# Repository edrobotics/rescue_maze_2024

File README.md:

# Rescue Maze 2024

Repository for ED Robotics' participation in the Robocup Junior Rescue Maze 2024 competition.

The contents of this repository were used in RoboCup Junior SM (Swedish Championships) 2024.

The code and CAD models are provided as-is, without any additional work done after the competition. The code (and hardware) did not work as expected, so keep that in mind.

## Performance

- RoboCupJunior Sweden 2024: Last place, 5 points :(

## Conclusions

Minimum Viable Product is a good idea that probably should have been prioritised more.

## Note:

This was our second year doing robotics. The code may contain trace amounts of spaghetti.

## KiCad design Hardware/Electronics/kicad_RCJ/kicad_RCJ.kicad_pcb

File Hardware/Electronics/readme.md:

# Electronics
In this folder, all electronics-related things are stored. This is mostly schematics and PCBs.

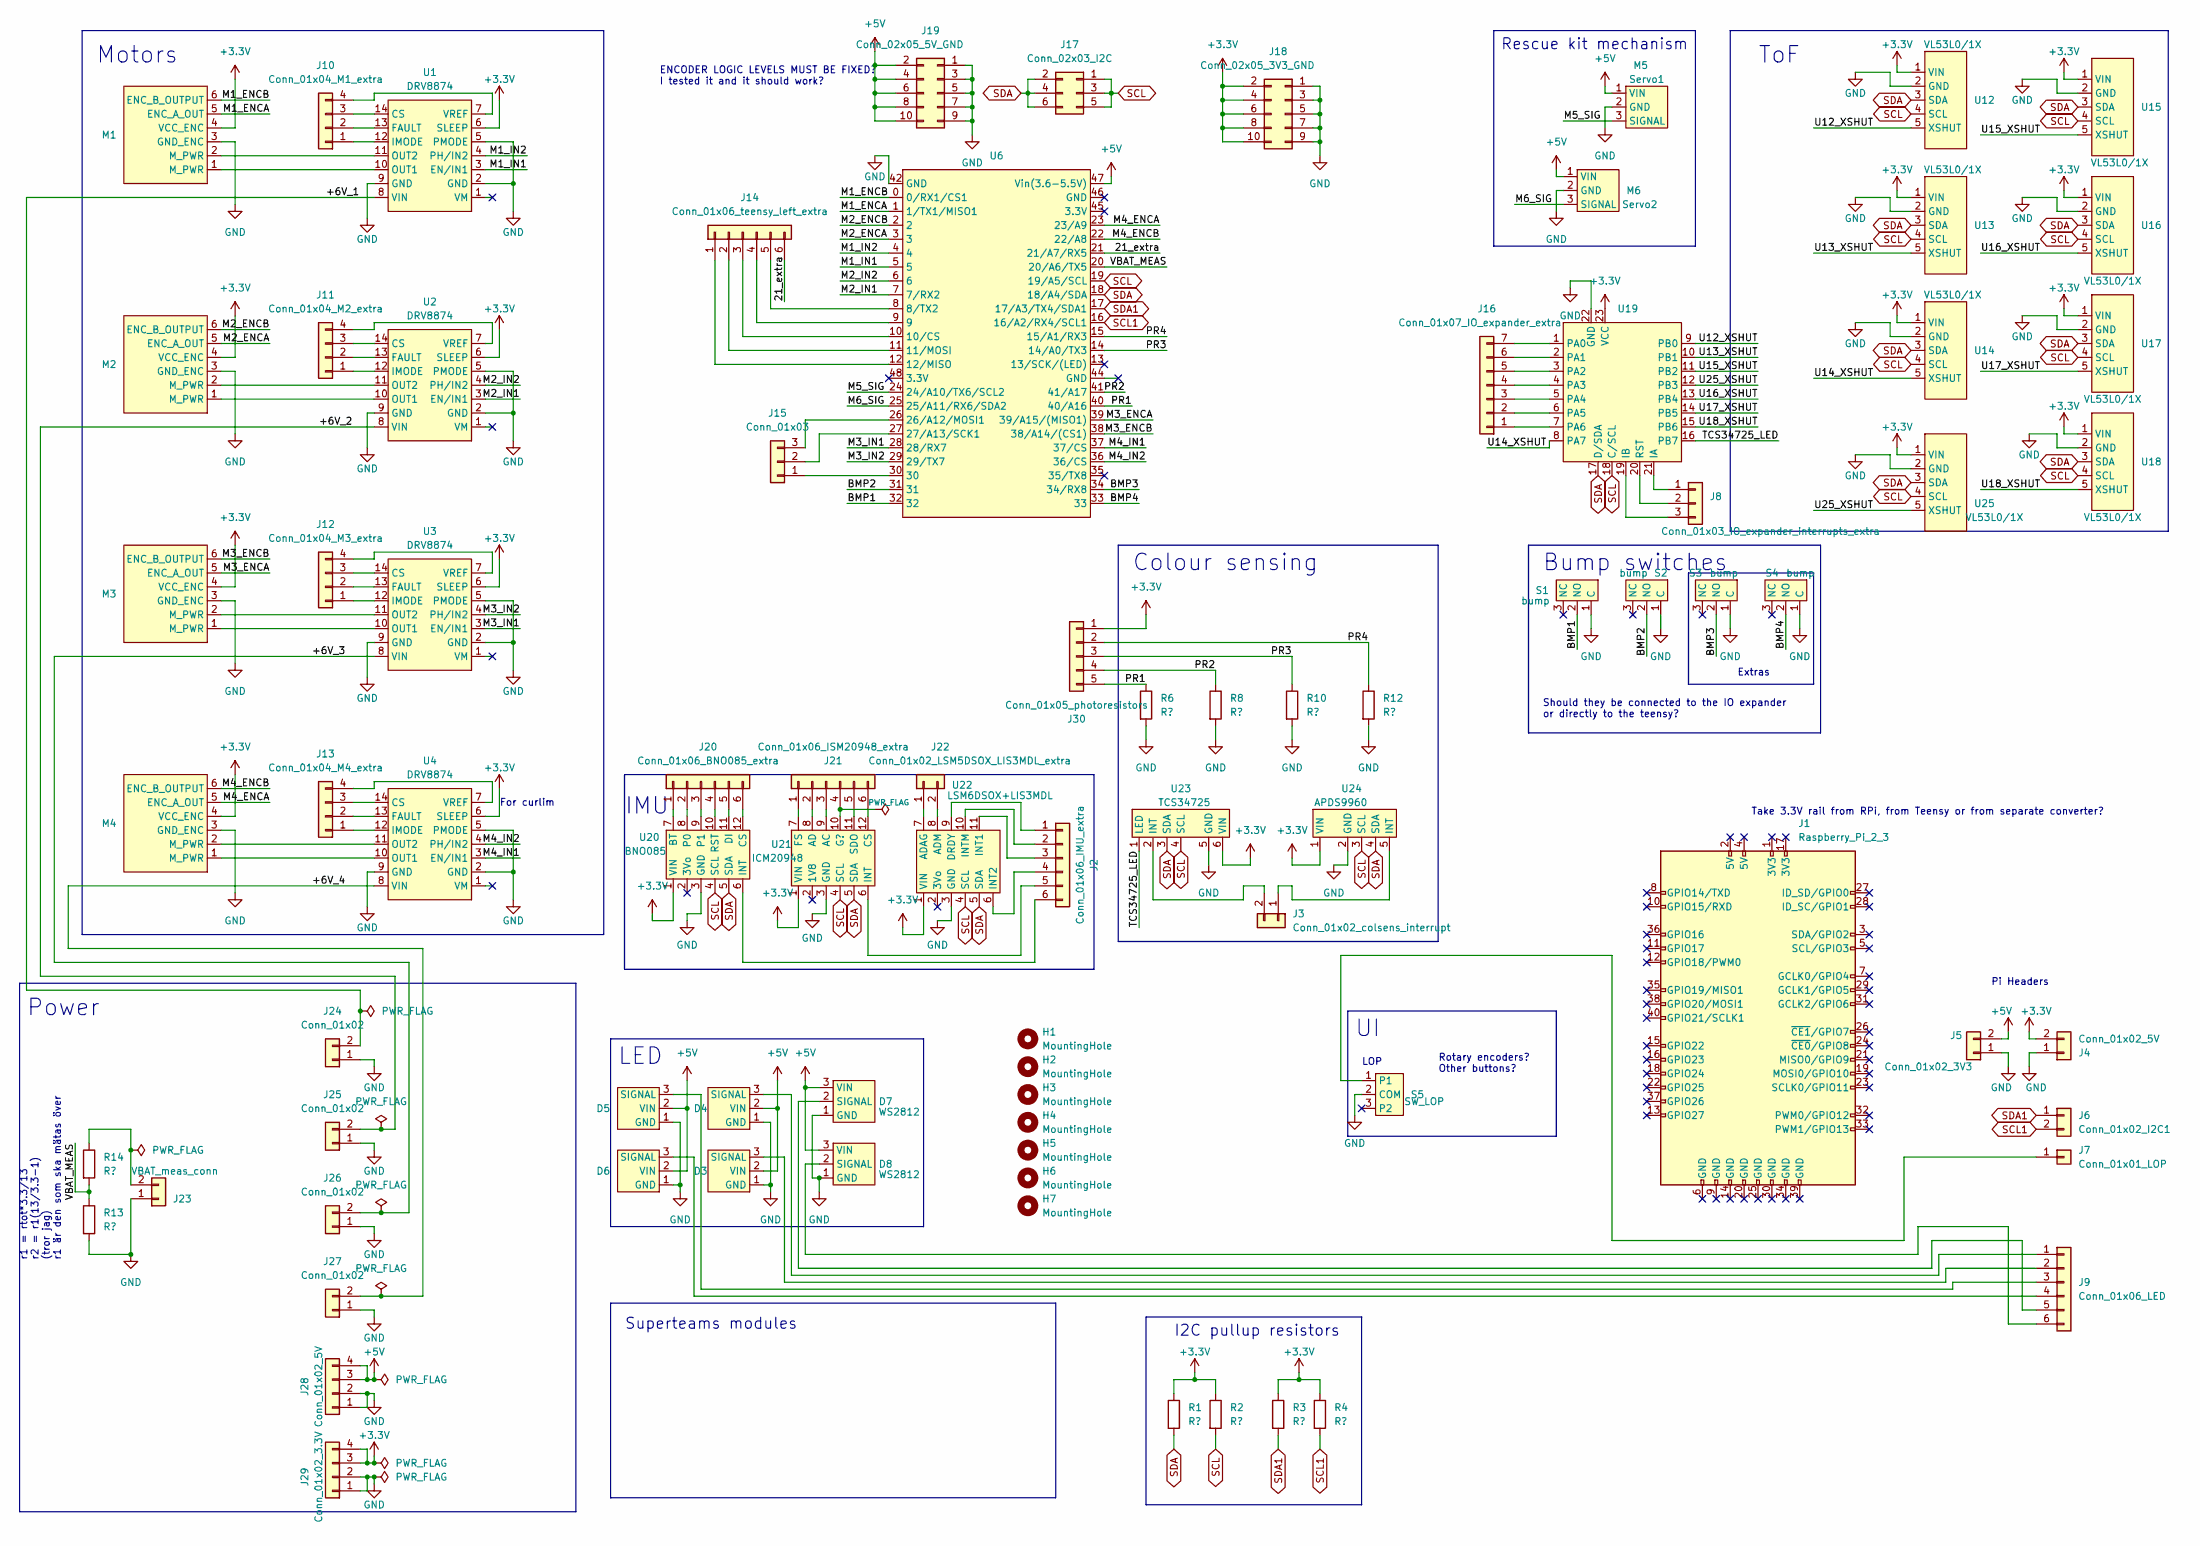
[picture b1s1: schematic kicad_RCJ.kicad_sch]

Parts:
D3, D4, D5, D6: PinSocket_1x03_P2.54mm_Vertical
D7, D8: WS2812; PinSocket_1x03_P2.54mm_Vertical
H1, H2, H3, H4, H5, H6, H7: MountingHole; MountingHole_3.2mm_M3
J1: Raspberry_Pi_2_3
J2: Conn_01x06_IMU_extra; PinSocket_1x06_P2.54mm_Vertical
J3: Conn_01x02_colsens_interrupt; PinSocket_1x02_P2.54mm_Vertical
J4: Conn_01x02_5V; JST_XH_B2B-XH-A_1x02_P2.50mm_Vertical
J5: Conn_01x02_3V3; JST_XH_B2B-XH-A_1x02_P2.50mm_Vertical
J6: Conn_01x02_I2C1; JST_XH_B2B-XH-A_1x02_P2.50mm_Vertical
J7: Conn_01x01_LOP; PinSocket_1x01_P2.54mm_Vertical
J8: Conn_01x03_IO_expander_interrupts_extra; PinSocket_1x03_P2.54mm_Vertical
J9: Conn_01x06_LED; PinSocket_1x06_P2.54mm_Vertical
J10: Conn_01x04_M1_extra; PinSocket_1x04_P2.54mm_Vertical
J11: Conn_01x04_M2_extra; PinSocket_1x04_P2.54mm_Vertical
J12: Conn_01x04_M3_extra; PinSocket_1x04_P2.54mm_Vertical
J13: Conn_01x04_M4_extra; PinSocket_1x04_P2.54mm_Vertical
J14: Conn_01x06_teensy_left_extra; PinSocket_1x06_P2.54mm_Vertical
J15: Conn_01x03; PinSocket_1x03_P2.54mm_Vertical
J16: Conn_01x07_IO_expander_extra; PinSocket_1x07_P2.54mm_Vertical
J17: Conn_02x03_I2C; PinSocket_2x03_P2.54mm_Vertical
J18: Conn_02x05_3V3_GND; PinSocket_2x05_P2.54mm_Vertical
J19: Conn_02x05_5V_GND; PinSocket_2x05_P2.54mm_Vertical
J20: Conn_01x06_BNO085_extra; PinSocket_1x06_P2.54mm_Vertical
J21: Conn_01x06_ISM20948_extra; PinSocket_1x06_P2.54mm_Vertical
J22: Conn_01x02_LSM5DSOX_LIS3MDL_extra; PinSocket_1x02_P2.54mm_Vertical
J23: VBAT_meas_conn; JST_XH_B2B-XH-A_1x02_P2.50mm_Vertical
J24, J25, J26, J27: Conn_01x02; JST_XH_B2B-XH-A_1x02_P2.50mm_Vertical
J28: Conn_01x02_5V; JST_XH_B4B-XH-A_1x04_P2.50mm_Vertical
J29: Conn_01x02_3.3V; JST_XH_B4B-XH-A_1x04_P2.50mm_Vertical
J30: Conn_01x05_photoresistors; JST_XH_B5B-XH-A_1x05_P2.50mm_Vertical
M1, M2, M3, M4: PinHeader_1x06_P2.54mm_Vertical
M5: Servo1; PinHeader_1x03_P2.54mm_Vertical
M6: Servo2; PinHeader_1x03_P2.54mm_Vertical
R1, R2, R3, R4, R6, R8, R10, R12, R13, R14: R?; R_Axial_DIN0207_L6.3mm_D2.5mm_P10.16mm_Horizontal
S1, S2, S3, S4: bump; JST_XH_B3B-XH-A_1x03_P2.50mm_Vertical
S5: SW_LOP; JST_XH_B3B-XH-A_1x03_P2.50mm_Vertical
U1, U2, U3, U4: DRV8874
U6: Teensy_41
U12, U13, U14, U15, U16, U17, U18, U25: VL53L0/1X; JST_XH_B5B-XH-A_1x05_P2.50mm_Vertical
U19: IO_Expander_nopower
U20: BNO085
U21: ICM20948; ICM2049
U22: LSM6DSOX+LIS3MDL
U23: TCS34725; JST_XH_B6B-XH-A_1x06_P2.50mm_Vertical
U24: APDS9960; JST_XH_B5B-XH-A_1x05_P2.50mm_Vertical

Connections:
+3.3V: J4.2, J18.2, J18.4, J18.6, J18.8, J18.10, J29.3, J29.4, J30.1, M1.4 (VCC_ENC), M2.4 (VCC_ENC), M3.4 (VCC_ENC), M4.4 (VCC_ENC), R1.1, R2.1, R3.1, R4.1, U1.6 (SLEEP), U2.6 (SLEEP), U3.6 (SLEEP), U4.6 (SLEEP), U12.1 (VIN), U13.1 (VIN), U14.1 (VIN), U15.1 (VIN), U16.1 (VIN), U17.1 (VIN), U18.1 (VIN), U19.23 (VCC), U20.1 (VIN), U21.1 (VIN), U22.1 (VIN), U23.6 (VIN), U24.1 (VIN), U25.1 (VIN)
+5V: D3.2 (VIN), D4.2 (VIN), D5.2 (VIN), D6.2 (VIN), D7.3 (VIN), D8.3 (VIN), J5.2, J19.2, J19.4, J19.6, J19.8, J19.10, J28.3, J28.4, M5.1 (VIN), M6.1 (VIN), U6.47 (Vin(3.6-5.5V))
/21_extra: J14.6, U6.21 (21/A7/RX5)
/+6V_1: J24.2, U1.8 (VIN)
/+6V_2: J25.2, U2.8 (VIN)
/+6V_3: J26.2, U3.8 (VIN)
/+6V_4: J27.2, U4.8 (VIN)
/BMP1: S1.2 (NO), U6.32
/BMP2: S2.2 (NO), U6.31
/BMP3: S3.2 (NO), U6.34 (34/RX8)
/BMP4: S4.2 (NO), U6.33
/M1_ENCA: M1.5 (ENC_A_OUT), U6.1 (1/TX1/MISO1)
/M1_ENCB: M1.6 (ENC_B_OUTPUT), U6.0 (0/RX1/CS1)
/M1_IN1: U1.3 (EN/IN1), U6.5
/M1_IN2: U1.4 (PH/IN2), U6.4
/M2_ENCA: M2.5 (ENC_A_OUT), U6.3
/M2_ENCB: M2.6 (ENC_B_OUTPUT), U6.2
/M2_IN1: U2.3 (EN/IN1), U6.7 (7/RX2)
/M2_IN2: U2.4 (PH/IN2), U6.6
/M3_ENCA: M3.5 (ENC_A_OUT), U6.39 (39/A15/(MISO1))
/M3_ENCB: M3.6 (ENC_B_OUTPUT), U6.38 (38/A14/(CS1))
/M3_IN1: U3.3 (EN/IN1), U6.28 (28/RX7)
/M3_IN2: U3.4 (PH/IN2), U6.29 (29/TX7)
/M4_ENCA: M4.5 (ENC_A_OUT), U6.23 (23/A9)
/M4_ENCB: M4.6 (ENC_B_OUTPUT), U6.22 (22/A8)
/M4_IN1: U4.3 (EN/IN1), U6.37 (37/CS)
/M4_IN2: U4.4 (PH/IN2), U6.36 (36/CS)
/M5_SIG: M5.3 (SIGNAL), U6.24 (24/A10/TX6/SCL2)
/M6_SIG: M6.3 (SIGNAL), U6.25 (25/A11/RX6/SDA2)
/PR1: J30.5, R6.1, U6.40 (40/A16)
/PR2: J30.4, R8.1, U6.41 (41/A17)
/PR3: J30.3, R10.1, U6.14 (14/A0/TX3)
/PR4: J30.2, R12.1, U6.15 (15/A1/RX3)
/TCS34725_LED: U19.16 (PB7), U23.1 (LED)
/U12_XSHUT: U12.5 (XSHUT), U19.9 (PB0)
/U13_XSHUT: U13.5 (XSHUT), U19.10 (PB1)
/U14_XSHUT: U14.5 (XSHUT), U19.8 (PA7)
/U15_XSHUT: U15.5 (XSHUT), U19.11 (PB2)
/U16_XSHUT: U16.5 (XSHUT), U19.13 (PB4)
/U17_XSHUT: U17.5 (XSHUT), U19.14 (PB5)
/U18_XSHUT: U18.5 (XSHUT), U19.15 (PB6)
/U25_XSHUT: U19.12 (PB3), U25.5 (XSHUT)
/VBAT_MEAS: R13.1, R14.2, U6.20 (20/A6/TX5)
GND: D3.1 (GND), D4.1 (GND), D5.1 (GND), D6.1 (GND), D7.1 (GND), D8.1 (GND), J4.1, J5.1, J18.1, J18.3, J18.5, J18.7, J18.9, J19.1, J19.3, J19.5, J19.7, J19.9, J23.1, J24.1, J25.1, J26.1, J27.1, J28.1, J28.2, J29.1, J29.2, M1.3 (GND_ENC), M2.3 (GND_ENC), M3.3 (GND_ENC), M4.3 (GND_ENC), M5.2 (GND), M6.2 (GND), R6.2, R8.2, R10.2, R12.2, R13.2, S1.1 (C), S2.1 (C), S3.1 (C), S4.1 (C), S5.2 (COM), U1.2 (GND), U1.5 (PMODE), U1.9 (GND), U2.2 (GND), U2.5 (PMODE), U2.9 (GND), U3.2 (GND), U3.5 (PMODE), U3.9 (GND), U4.2 (GND), U4.5 (PMODE), U4.9 (GND), U6.42 (GND), U12.2 (GND), U13.2 (GND), U14.2 (GND), U15.2 (GND), U16.2 (GND), U17.2 (GND), U18.2 (GND), U19.22 (GND), U20.3 (GND), U21.3 (GND), U22.3 (GND), U23.5 (GND), U24.2 (GND), U25.2 (GND)
unnamed: D3.3 (SIGNAL), J9.2
unnamed: D4.3 (SIGNAL), J9.1
unnamed: D5.3 (SIGNAL), J9.3
unnamed: D6.3 (SIGNAL), J9.4
unnamed: D7.2 (SIGNAL), J9.5
unnamed: D8.2 (SIGNAL), J9.6
unnamed: J2.1, U22.9 (DRDY)
unnamed: J2.2, U22.10 (INTM)
unnamed: J2.3, U22.11 (INT1)
unnamed: J2.4, U22.6 (INT2)
unnamed: J2.5, U21.6 (INT)
unnamed: J2.6, U20.6 (INT)
unnamed: J3.1, U24.5 (INT)
unnamed: J3.2, U23.2 (INT)
unnamed: J7.1, S5.1
unnamed: J8.1, U19.21 (IA)
unnamed: J8.2, U19.20 (RST)
unnamed: J8.3, U19.19 (IB)
unnamed: J10.1, U1.12 (IMODE)
unnamed: J10.2, U1.13 (FAULT)
unnamed: J10.3, U1.14 (CS)
unnamed: J10.4, U1.7 (VREF)
unnamed: J11.1, U2.12 (IMODE)
unnamed: J11.2, U2.13 (FAULT)
unnamed: J11.3, U2.14 (CS)
unnamed: J11.4, U2.7 (VREF)
unnamed: J12.1, U3.12 (IMODE)
unnamed: J12.2, U3.13 (FAULT)
unnamed: J12.3, U3.14 (CS)
unnamed: J12.4, U3.7 (VREF)
unnamed: J13.1, U4.12 (IMODE)
unnamed: J13.2, U4.13 (FAULT)
unnamed: J13.3, U4.14 (CS)
unnamed: J13.4, U4.7 (VREF)
unnamed: J14.1, U6.12 (12/MISO)
unnamed: J14.2, U6.11 (11/MOSI)
unnamed: J14.3, U6.10 (10/CS)
unnamed: J14.4, U6.9
unnamed: J14.5, U6.8 (8/TX2)
unnamed: J15.1, U6.30
unnamed: J15.2, U6.27 (27/A13/SCK1)
unnamed: J15.3, U6.26 (26/A12/MOSI1)
unnamed: J16.1, U19.7 (PA6)
unnamed: J16.2, U19.6 (PA5)
unnamed: J16.3, U19.5 (PA4)
unnamed: J16.4, U19.4 (PA3)
unnamed: J16.5, U19.3 (PA2)
unnamed: J16.6, U19.2 (PA1)
unnamed: J16.7, U19.1 (PA0)
unnamed: J20.1, U20.7 (BT)
unnamed: J20.2, U20.8 (P0)
unnamed: J20.3, U20.9 (P1)
unnamed: J20.4, U20.10 (RST)
unnamed: J20.5, U20.11 (DI)
unnamed: J20.6, U20.12 (CS)
unnamed: J21.1, U21.7 (FS)
unnamed: J21.2, U21.8 (AD)
unnamed: J21.3, U21.9 (AC)
unnamed: J21.4, U21.10 (G?)
unnamed: J21.5, U21.11 (SDO)
unnamed: J21.6, U21.12 (CS)
unnamed: J22.1, U22.7 (ADAG)
unnamed: J22.2, U22.8 (ADM)
unnamed: J23.2, R14.1
unnamed: M1.1 (M_PWR), U1.10 (OUT1)
unnamed: M1.2 (M_PWR), U1.11 (OUT2)
unnamed: M2.1 (M_PWR), U2.10 (OUT1)
unnamed: M2.2 (M_PWR), U2.11 (OUT2)
unnamed: M3.1 (M_PWR), U3.10 (OUT1)
unnamed: M3.2 (M_PWR), U3.11 (OUT2)
unnamed: M4.1 (M_PWR), U4.10 (OUT1)
unnamed: M4.2 (M_PWR), U4.11 (OUT2)
SCL: J17.1, J17.3, J17.5, R2.2, U6.19 (19/A5/SCL), U12.4 (SCL), U13.4 (SCL), U14.4 (SCL), U15.4 (SCL), U16.4 (SCL), U17.4 (SCL), U18.4 (SCL), U19.18 (C/SCL), U20.4 (SCL), U21.4 (SCL), U22.4 (SCL), U23.4 (SCL), U24.3 (SCL), U25.4 (SCL)
SCL1: J6.2, R4.2, U6.16 (16/A2/RX4/SCL1)
SDA: J17.2, J17.4, J17.6, R1.2, U6.18 (18/A4/SDA), U12.3 (SDA), U13.3 (SDA), U14.3 (SDA), U15.3 (SDA), U16.3 (SDA), U17.3 (SDA), U18.3 (SDA), U19.17 (D/SDA), U20.5 (SDA), U21.5 (SDA), U22.5 (SDA), U23.3 (SDA), U24.4 (SDA), U25.3 (SDA)
SDA1: J6.1, R3.2, U6.17 (17/A3/TX4/SDA1)

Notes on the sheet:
IMU
Motors
r1 = rtot*3.3/13 r2 = r1(13/3.3-1) (tror jag) r1 är den som ska mätas över
Take 3.3V rail from RPi, from Teensy or from separate converter?
ENCODER LOGIC LEVELS MUST BE FIXED? I tested it and it should work?
ToF
Extras
Power
LED
Superteams modules
Rotary encoders? Other buttons?
Colour sensing
Rescue kit mechanism
Should they be connected to the IO expander or directly to the teensy?
For curlim
Pi Headers
LOP
Bump switches
I2C pullup resistors

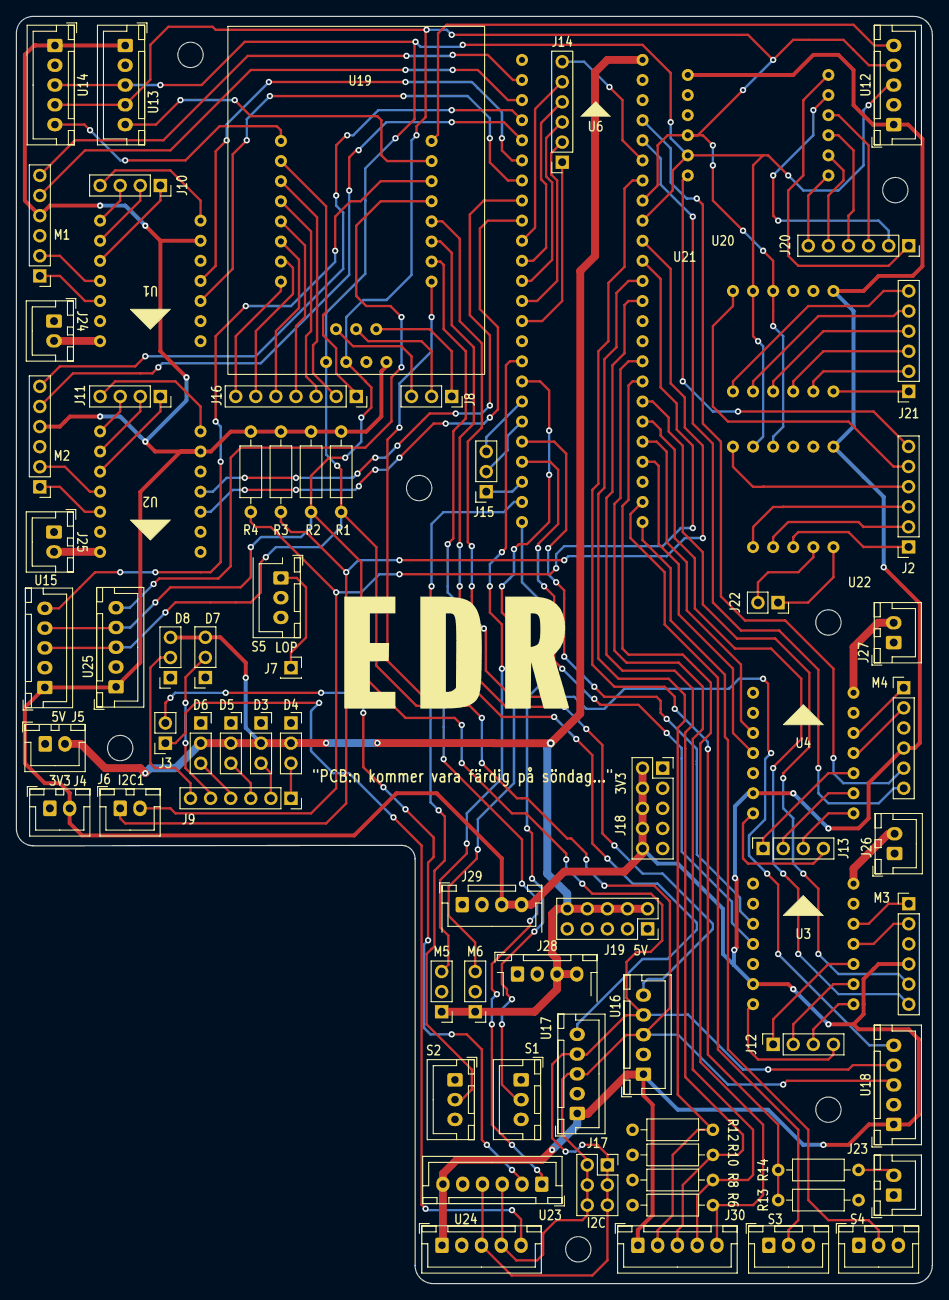
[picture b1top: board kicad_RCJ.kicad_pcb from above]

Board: 2 copper layers, 115.8 x 160.2 mm, 82 parts (0 on the bottom side), 120 nets.

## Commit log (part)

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2023-08-29 initial commit in vision
2023-08-29 and again
2023-09-16 added .gitignore for CAD files
2023-10-21 added electronics folder and readme
2023-10-29 added some self-calibration for pwm to rpm curves and also did some other stuff
2023-10-29 fixed encoder position overflow bug and rpm to pwm translation, so the essentials work.
2023-10-29 updated notes and added curve fitting library
2023-11-03 added I2C pullup resistors and I2C between teensy and pi
2023-11-03 added voltage divider and measurement for battery voltage
2023-11-16 schematic finished?
2023-11-18 clarified schematic and added some headers
2023-11-21 added some footprints and did some PCB layout work
2023-11-22 worked on PCB layout, made footprints etc.
2023-11-23 Added lidar and mazenav dir
2023-11-23 refined PCB layout and resolved some footprint issues
2023-11-23 Updated gitignore
2023-11-26 Fixed the script idiot
2023-11-26 add executable and changed its filename
2023-11-30 added size constraints to PCB outline and changed layout accordingly
2023-12-01 added courtyards to most custom footprints
2023-12-01 updated PCB STEP for test in CAD
2023-12-02 added some 3d-mmodels to footprints in PCB
2023-12-02 added 3d model for IO expander (something slightly off, keep in mind)
2023-12-03 enlarged PCB outline and rearranged
2023-12-03 enlarged resistor footprint
2023-12-06 continued routing of outer sections and rearranged parts of schematic for better routing
2023-12-07 PCB finished?
2023-12-08 Created mazenav base files
2023-12-08 Added mazenav build script
2023-12-11 Made more logging and starting from log data possible
2023-12-14 Added example scan folder and updated gitignore, tried new line things
2023-12-19 Color Vision Script
    Testing and special cases are yet to be done
2023-12-20 added communication description
2023-12-21 fixed build script
2023-12-21 fixed build script again (better debugging)
2023-12-21 added ramp examples
2023-12-26 for testing
2023-12-28 the support code is working now
2023-12-29 fixed stall issue with motors
2023-12-29 cleaned up motor controller code
2023-12-29 added sync script to sync mazenav to pi
2023-12-29 added some i2c and motor control code for teensy
2023-12-30 added build script task in vscode
2023-12-30 Added tile class and map bit enum
2023-12-31 Fixed line merging, more comments
2023-12-31 Fix tileed definitions in globalNav
2024-01-01 remade i2c communication data format
2024-01-02 spaghetti monster (I2C code) now works in basic tests
2024-01-07 added untested code for ToF
2024-01-09 added battery voltage measurement code
2024-01-09 finished ToF code(?)
2024-01-09 definded Teensy-Pi communication
2024-01-11 added test sensor. Should be ready for simple test
2024-01-13 added other basic sensor files and classes (just skeleton, nowhere near done)
2024-01-14 Basic wall following (without communication)
2024-01-14 Created communicator files, namespace, and some classes, functions and members
2024-01-20 fixed some general issues and commented code (still issues left, will not compile)
2024-01-20 added more sensors
2024-01-20 restructured fusion program and added mutexes
2024-01-20 fixed compilation issue by passing pointer to communication object
2024-01-23 began local navigation path planner
2024-01-24 futher developed pathplanning
2024-01-25 structured global communication and tested teensy communication
2024-01-26 commented out unfinished code
2024-01-28 fixed transforms (?)(kind of) and some pedantic errors
2024-01-30 hopefully fixed motor control bug (untested) (still need control system)
2024-02-01 developed path planner
2024-02-13 added optimized transform methods to transform system
2024-02-13 added child structure to tfsys
2024-02-14 fixed transform system (can still polish) and ghost-move
2024-02-15 finished kinematic driver (untested)
2024-02-17 Cleaned up code
2024-02-18 Fixed inevitble bugs, should be the same as before file split now
2024-02-21 Created lidar code folder, moved files
2024-02-29 added PID controller, added PID to kinematicdriver, misc. work on pathplanner/-follower. NO IDEA IF WORKING (PROBABLY NOT)
2024-03-06 updated PoseCommunicator to include speeds
2024-03-06 wrote framework for sensor fusion
2024-03-09 Vision communication should be mostly done, but might need to transform XY from camera to robot
2024-03-10 implemented some contribution calculations for PoseEstimator (not done)
2024-03-30 Updated VisionCommunicator, still a bit badly structured and needs testing
2024-04-02 New files, structure and standardising
2024-04-03 restuctured fusion algorithm and developed it further (not done yet)
2024-04-04 fixed pose wrapping
2024-04-04 made transform system thread safe (i think/hope)
2024-04-04 integraped PoseEstimator into fusion main loop for testing
2024-04-08 Build file now creates build directory
2024-04-08 updated PID controller to allow restarting
2024-04-08 fixed mutex lock loop causing problems
2024-04-08 added the tensorflow section into the code, aswell as somesmall exception handling
2024-04-09 Created Lidar class for mergeability with mazeNav
2024-04-09 fixed warnings regarding Transform assignment and copy
2024-04-09 updated PathFollower to do simpler PID following instead. Not done (control flow, knowing when done and turning left (at least))
2024-04-09 Added missing inclusion protection
2024-04-10 Finished implementing navigation
2024-04-10 fixed simple compilation and linking issues. Still problems with inline functions in Tile class
2024-04-10 added time averages to ToF data
2024-04-11 Fixed weird inlining issue and instantating tiles in map
2024-04-11 updated build.sh to tell you if it compiled or not
2024-04-11 fixed averaging problems with ToF (and IMU) and implemented wanted lag
2024-04-11 fixed probably bug in pathFollower targetPoint distance/angle calculations
2024-04-11 commit before restoring
2024-04-11 greatly improved tile switch detection
2024-04-11 Fixed AStar again
2024-04-11 fixed wrapping issue in updatePoseComm
2024-04-12 made everything run aswell as integrating communication(untested)
2024-04-12 fixed weird values due to incomplete switch to probabilithy model
2024-04-12 improved PoseEstimator with corrected pose wrapping and misc. other stuff
2024-04-12 added taking account for wall thickness
2024-04-12 fixed pose updating wrapping bug
2024-04-13 moved and added PID loops to PathFollower
2024-04-13 fixed robot speed calculation
2024-04-13 added time averages to robot Speed calculation
2024-04-13 made PathFollower wait for PoseComm to be updated
2024-04-13 fixed motor PID loop
2024-04-13 removed old warning for PID tuning
2024-04-14 tuned some (not all) PID constants and fixed some things for driving
2024-04-14 fixed tof abs trans y bug which accepted too large values and also bug with values of 0
2024-04-14 fixed other tof y abs bug
2024-04-14 made raspberrypi compatible, made code to exctract victim to use for training
2024-04-14 Add files via upload
    Square Detection Test (works only on Red and Green and not shaky images)
2024-04-15 Close to final code -> Read caption
    Close to final code for Linköping IF it is possible for the camera to take a not-shaky-photo when it passes each victim.
    Else
    1. You could try to allow more shaky images for the square detection, but then the risk is that the code becomes more unreliable
    2. Base the detection on thresholds and white scale, i.e. adjust uploaded ColorDetection code to be used as final code or use the code from previous year.
    Status of the code in this commit:
    - Can't detect shaky images
2024-04-15 fixed IMU reset issue
2024-04-16 improved IMU issue?
2024-04-16 added remote control and improved pid loop?
2024-04-16 Fixed forgotten namespace usage
2024-04-16 added non-working LED code (works with command line tools though, but why not here?)
2024-04-17 FinalColoredVictimLinköping
2024-04-17 TestFolder
2024-04-17 One more time...
2024-04-17 Why isn't this working
2024-04-17 (Final) ColoredVictimCode for Linköping
    Implement DetectColor in the main vision code to use the class in the script ColorDetection
    Implement DetectColoredSquare in the main vision code to use the class in the script ColoredSquareDetection
    Code status:
    - Crop image implemented in both scripts but commented out, if needed to only see the wall we can adjust this
    Possible game plan:
    - We should be able to switch between these two scripts, so both needs to be tested.
2024-04-17 Added communication and mapping, everything that needs to be done is done
2024-04-17 Fixed wiringpi setup in LedControl
2024-04-17 added tileDrivePropertyCommunicator to localNav and fixed compilation issue with wiringPi
2024-04-17 implemented init driveCommand in localNav/fusion
2024-04-17 Fixed logger more
2024-04-17 changed led control
2024-04-17 Fixed segmentation faults and memory issues in AStar
2024-04-17 fixed bug where panicFlags status was not updated to read
2024-04-17 Tile property logging, deleted unused function
2024-04-17 Added stuff for test
2024-04-17 added pose flushing
2024-04-17 Print on init
2024-04-17 added first version of port of colour sensor driver
2024-04-17 images for testing
2024-04-17 added readme for starting vision code
2024-04-18 probably fixed flush hanging bug
2024-04-18 cleanup and added small sleep times for optimization
2024-04-18 removed scary character
2024-04-18 made readabilyt easier when testing the code
2024-04-18 Fixed turn issue and ramp paths, made g++ turn missing returns to errors
2024-04-18 fixed PoseEstimator incremental calc and obstacle detection stopping
2024-04-18 Fixed segmentation fault in logging mazePath
2024-04-18 added debugging info and maybe fixed flush
2024-04-18 added missing mutex to flushDone()
2024-04-18 restructured PoseCommunicator and MotorControllerCommunicator into their own files
2024-04-18 Made visionCommunicator not crash on empty victims
2024-04-18 Added temporary debugging
2024-04-18 Partial revert of aforementioned non-profitable inversion fix, if completion possibility is comprehensible
2024-04-18 Added functions for (unimplemented) ability to ignore non-wall victims
2024-04-18 implemented turnBack driveCommand (untested)
2024-04-18 Fixed camera indexes
2024-04-18 Added lidar files
2024-04-18 adapted PoseEstimator to new PoseComm structure
2024-04-18 Improved behavior when drive did not drive the driving
2024-04-18 Added logging and delay when finishing
2024-04-19 fixed issue arising from merge and added flushing after drive, before filling tileInfo
2024-04-19 Logging should have worked before, but should absolutely work now
2024-04-19 Added new panicflag for when we have driven half the tile
2024-04-19 added more log images
2024-04-19 logging changes thresholds
2024-04-19 finished (?) colour detection (no calibration) and added testing to PoseEstimator
2024-04-19 config
2024-04-19 Made previous fix fix code in mazeav also
2024-04-19 finished (?) colour calibration as well
2024-04-19 Added comment trying to compensate for bad code
2024-04-19 got current Tile colour working for black, blue and white (reflective is giving issues)
2024-04-19 fixed colour threshold storing and another threshold determination bug
2024-04-19 Changed behavior on wallFollowing and added going to wallFollowing on LOP
2024-04-19 fixed naming issue with colour threshold file name
2024-04-19 added panic behaviours to PoseEstimator and PathFollower
2024-04-19 fixed so only detect black tile when driving forwards
2024-04-19 did fixes to driving backwards
2024-04-19 fixed stepDriven bug with inverted values
2024-04-20 Made better implementation of timer
2024-04-20 fixed misc. colour and other PoseEstimator bugs
2024-04-20 Removed e.what, as they might have caused segFaults
2024-04-20 Added long wait for segFault debugging, but in the right place this time maybe
2024-04-20 Fixed victim handling by doing a switcharoo
2024-04-20 Removed lidar files as they will not be used anyway
2024-04-20 Changed in other cpp file also, wow
2024-04-20 Added panic flag for getting off ramp
2024-04-20 added ramp driving to localnav and fusion (still needs more work)
2024-04-20 added wallStates getter and setter and implemented blue tiles
2024-04-20 Now visionComm checks for wall in victim direction
2024-04-20 Made only leftwall follower
2024-04-20 Only leftwall follower now
2024-04-20 second run code
2024-04-20 added support for blue tiles
2024-04-20 Fixed strange flag behavior
2024-04-20 removed frY and readded bY ToF sensor, as it did not work
2024-04-20 fixed inversion of ToF sensors
